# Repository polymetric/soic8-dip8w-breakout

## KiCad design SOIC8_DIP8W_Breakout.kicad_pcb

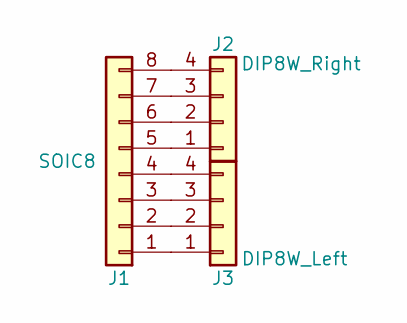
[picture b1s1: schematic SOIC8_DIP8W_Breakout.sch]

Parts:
J1: SOIC8; SOIC-8_3.9x4.9mm_Pitch1.27mm
J2: DIP8W_Right; 0.1in_0x1_header
J3: DIP8W_Left; 0.1in_0x1_header

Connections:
unnamed: J1.1, J3.1
unnamed: J1.2, J3.2
unnamed: J1.3, J3.3
unnamed: J1.4, J3.4
unnamed: J1.5, J2.1
unnamed: J1.6, J2.2
unnamed: J1.7, J2.3
unnamed: J1.8, J2.4

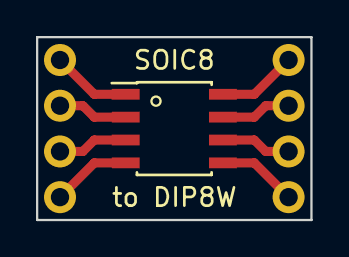
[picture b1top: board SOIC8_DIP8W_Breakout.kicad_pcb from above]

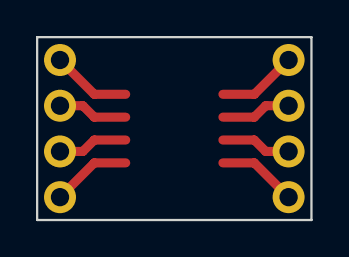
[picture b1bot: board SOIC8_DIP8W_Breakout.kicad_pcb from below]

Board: 2 copper layers, 15.2 x 10.2 mm, 3 parts (2 on the bottom side), 8 nets.
